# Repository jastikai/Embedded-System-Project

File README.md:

# EmbeddedSystemProject
Repository for Embedded System Project course of University of Oulu, Spring 2024.

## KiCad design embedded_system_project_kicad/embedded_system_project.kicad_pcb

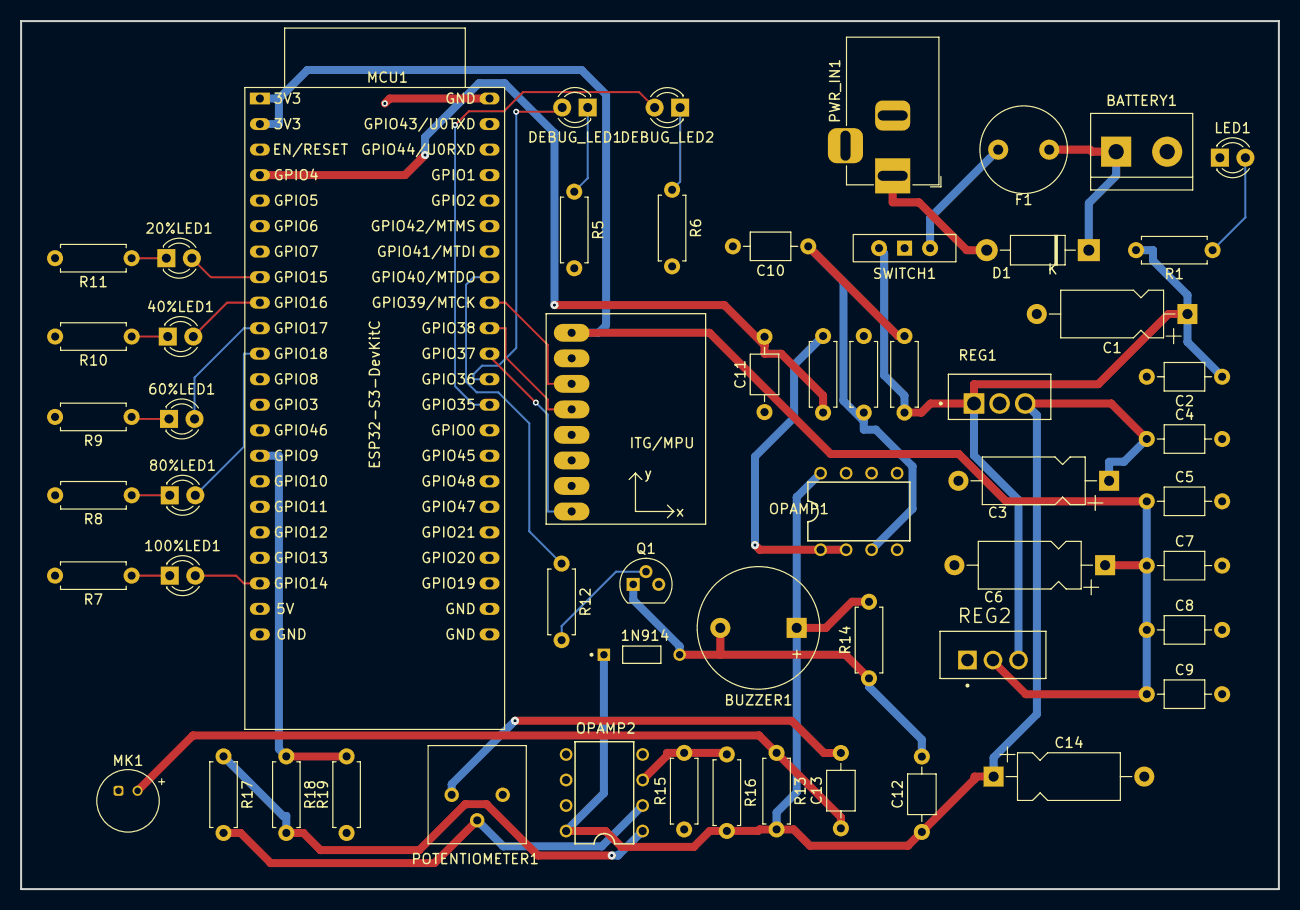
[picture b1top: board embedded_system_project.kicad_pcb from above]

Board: 2 copper layers, 125.2 x 86.4 mm, 57 parts (0 on the bottom side), 37 nets.

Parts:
1N914: D2; DIOAD753W49L380D172B
20%LED1, 40%LED1: LED_RED; LED_D3.0mm_Clear
60%LED1: LED_BLUE; LED_D3.0mm_Clear
80%LED1, 100%LED1: LED_GREEN; LED_D3.0mm_Clear
BATTERY1: TBLOCK-X2; TerminalBlock_bornier-2_P5.08mm
BUZZER1: 2300Hz; Buzzer_12x9.5RM7.6
C1, C3, C6, C14: 1000 microF; CP_Axial_L10.0mm_D4.5mm_P15.00mm_Horizontal
C2, C4, C7, C8, C9, C10, C11, C12, C13: 100 nF; C_Axial_L3.8mm_D2.6mm_P7.50mm_Horizontal
C5: 1 microF; C_Axial_L3.8mm_D2.6mm_P7.50mm_Horizontal
D1: 1N4007; D_DO-41_SOD81_P10.16mm_Horizontal
DEBUG_LED1, DEBUG_LED2: LED_RED; LED_D3.0mm
F1: 1A; Fuse_Littelfuse_372_D8.50mm
GYRO1: GY-521
LED1: LED_RED; LED_D3.0mm
MCU1: ESP32-S3-DevKitC
MK1: Microphone_Condenser; POM-2244P-C3310-2-R
OPAMP1, OPAMP2: LM358; DIL08
POTENTIOMETER1: R_3386P, 100k; Potentiometer_Bourns_3386P_Vertical
PWR_IN1: DC 2.0mm; BarrelJack_Horizontal
Q1: 2N2222A; TO-92
R1: 4.7k; R_Axial_DIN0207_L6.3mm_D2.5mm_P7.62mm_Horizontal
R2: 8.6k; R_Axial_DIN0207_L6.3mm_D2.5mm_P7.62mm_Horizontal
R3: 5k; R_Axial_DIN0207_L6.3mm_D2.5mm_P7.62mm_Horizontal
R4, R15: 10k; R_Axial_DIN0207_L6.3mm_D2.5mm_P7.62mm_Horizontal
R5, R6, R7, R8, R9, R10, R11, R12, R13, R14, R18: 1k; R_Axial_DIN0207_L6.3mm_D2.5mm_P7.62mm_Horizontal
R16: 20k; R_Axial_DIN0207_L6.3mm_D2.5mm_P7.62mm_Horizontal
R17: 1M; R_Axial_DIN0207_L6.3mm_D2.5mm_P7.62mm_Horizontal
R19: 2k; R_Axial_DIN0207_L6.3mm_D2.5mm_P7.62mm_Horizontal
REG1: L7805; TO255P1020X450X2000-3
REG2: LM1085-3.3; TO254P1054X470X1955-3
SWITCH1: Switch; SW_Slide-03_Wuerth-WS-SLTV_10x2.5x6.4_P2.54mm

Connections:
3V3: C5.1, C6.1, C7.1, C8.1, C9.1, GYRO1.VCC, MCU1.1 (3V3), MCU1.2 (3V3), REG2.2 (VO)
5V: 1N914.K, BUZZER1.1 (+), C3.1, C4.1, C12.1, C14.1, OPAMP1.8, OPAMP2.8, R13.2, R14.2, R16.2, REG1.3 (OUT)
8V5: C1.1, C2.1, R1.2, R2.2, REG1.1 (IN), REG2.3 (VI), SWITCH1.3 (A)
20%LED: 20%LED1.2 (A), MCU1.8 (GPIO15/ADC2_CH4/32K_P)
40%LED: 40%LED1.2 (A), MCU1.9 (GPIO16/ADC2_CH5/32K_N)
60%LED: 60%LED1.2 (A), MCU1.10 (GPIO17/ADC2_CH6)
80%LED: 80%LED1.2 (A), MCU1.11 (GPIO18/ADC2_CH7)
100%LED: 100%LED1.2 (A), MCU1.20 (GPIO14/ADC2_CH3)
BUZZER: MCU1.37 (GPIO40/MTDO), R12.1
BattSignal: C11.2, MCU1.4 (GPIO4/ADC1_CH3), R4.2
DEBUG_LED1: DEBUG_LED1.2 (A), MCU1.33 (GPIO36)
DEBUG_LED2: DEBUG_LED2.2 (A), MCU1.32 (GPIO35)
GND: BATTERY1.2, C1.2, C2.2, C3.2, C4.2, C5.2, C6.2, C7.2, C8.2, C9.2, C10.2, C11.1, C14.2, GYRO1.ADO, GYRO1.GND, GYRO1.XCL, GYRO1.XDA, LED1.1 (K), MCU1.22 (GND), MCU1.23 (GND), MCU1.24 (GND), MCU1.44 (GND), MK1.1 (-), OPAMP1.4, OPAMP2.4, POTENTIOMETER1.3, PWR_IN1.2, Q1.3 (E), R3.1, R5.2, R6.2, R7.2, R8.2, R9.2, R10.2, R11.2, R15.1, R19.1, REG1.2 (GND), REG2.1 (GND)
MIC_ADC: MCU1.15 (GPIO9/ADC1_CH8), R18.1, R19.2
MPU_INT: GYRO1.INT, MCU1.34 (GPIO37)
MPU_SCL: GYRO1.SCL, MCU1.36 (GPIO39/MTCK)
MPU_SDA: GYRO1.SDA, MCU1.35 (GPIO38)
unnamed: 1N914.A, BUZZER1.2 (-), C12.2, Q1.1 (C), R14.1
unnamed: 20%LED1.1 (K), R11.1
unnamed: 40%LED1.1 (K), R10.1
unnamed: 60%LED1.1 (K), R9.1
unnamed: 80%LED1.1 (K), R8.1
unnamed: 100%LED1.1 (K), R7.1
unnamed: BATTERY1.1, D1.1 (K), F1.1
unnamed: C13.2, POTENTIOMETER1.1
unnamed: D1.2 (A), PWR_IN1.1
unnamed: DEBUG_LED1.1 (K), R5.1
unnamed: DEBUG_LED2.1 (K), R6.1
unnamed: LED1.2 (A), R1.1
unnamed: C13.1, MK1.2 (+), R13.1
unnamed: C10.1, OPAMP1.3 (+), R2.1, R3.2
unnamed: OPAMP1.1, OPAMP1.2 (-), R4.1
unnamed: OPAMP2.1, R17.1, R18.2
unnamed: OPAMP2.3 (+), R15.2, R16.1
unnamed: OPAMP2.2 (-), POTENTIOMETER1.2, R17.2
unnamed: Q1.2 (B), R12.2
unnamed: F1.2, SWITCH1.2 (B)

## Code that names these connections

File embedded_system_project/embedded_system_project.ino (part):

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// Pin definitions
#define MIC_PIN           9    // ADC1 channel for microphone input
#define BATTERY_PIN       4    // ADC1 channel for battery voltage
#define BUZZER_PIN        40   // DAC output for buzzer
#define LED_20            15   // LED for 20% battery level
#define LED_40            16   // LED for 40% battery level
#define LED_60            17   // LED for 60% battery level
#define LED_80            18   // LED for 80% battery level
#define LED_100           14   // LED for 100% battery level
#define DEBUG_LED1        36   // LED for debugging
#define DEBUG_LED2        35   // LED for debugging

// MPU6050 Pin definitions
#define MPU_SCL           39   // MPU SCL
#define MPU_SDA           38   // MPU SDA
#define MPU_INT           37   // MPU INT

// Battery voltage calibration
#define BATTERY_FULL_VOLTAGE 3.0
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float accelXOffset = 0, accelYOffset = 0, accelZOffset = 0;

void setup() {
  pinMode(DEBUG_LED1, OUTPUT);
  pinMode(DEBUG_LED2, OUTPUT);
  digitalWrite(DEBUG_LED1, LOW);
  digitalWrite(DEBUG_LED2, LOW);
  digitalWrite(DEBUG_LED1, HIGH);
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  }

  // Initialize MPU6050
  Wire.begin(MPU_SDA, MPU_SCL);  // Initialize I2C with defined pins
  for (int i = 0; i < 5; i++) { // Retry up to 5 times
    if (mpu.begin()) {
      Serial.println("MPU6050 initialized successfully");
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
// Play an alert beep
void playAlertBeep() {
  tone(BUZZER_PIN, 1000, 500);  // 1000 Hz for 500 ms
  delay(500);
}

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// Play a success beep
void playSuccessBeep() {
  for (int freq = 1000; freq <= 2000; freq += 250) {
    tone(BUZZER_PIN, freq, 100);
    delay(150);
  }
}
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
  for (int thisNote = 0; thisNote < 8; thisNote++) {
    int noteDuration = noteDurations[thisNote];
    tone(BUZZER_PIN, melody[thisNote], noteDuration);
    delay(noteDuration * 1.3);  // to distinguish the notes
  }
}
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
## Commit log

2024-02-23 Create work_log
2024-05-13 Started main script of the project
2024-08-10 First PoC of full game with controller
    This version has a working mqtt messaging scheme between the Python game and the ESP32 wireless controller. It needs now sensors to actually read and write data.
2024-11-10 Changes to code
2024-11-10 blabla
2025-01-11 Updated repo
